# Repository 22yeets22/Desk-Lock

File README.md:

# Desk-Lock

A cheap desk lock that unlocks with an NFC card.

## Overview

This project is a DIY desk lock which keeps items in your desk secure by using a NFC reader. An ESP32 reads an NFC card via a PN532 module and controls a servo motor that locks or unlocks the desk. A photoresistor is used to detect when the drawer is closed so it can relock automatically.

[Detailed Description Here](#Detailed-Description)

## Motivation

I wanted a secure way to lock my desk because I keep important items inside and my little brother cannot be trusted with it. Buying a commercial lock felt boring and expensive, so building one with NFC was more interesting and let me design my own NFC card and reader.

## Parts List (Bill of Materials)

- 1x of [Photoresistor](https://www.aliexpress.us/item/3256805782399608.html), TYPE 5528, PRICE $2.39
- 1x of [10k Resistor](https://www.aliexpress.us/item/2251832766343175.html), TYPE 10K, PRICE $1.25
- 1x of [MG996R Servo](https://www.aliexpress.us/item/3256808293405785.html), TYPE N/A, PRICE $0.99
- 1x of [AC to DC Power Supply](https://www.aliexpress.us/item/3256806901002886.html), TYPE US Plug/DC 5V/4A, PRICE $4.60
- 1x of [ESP32 Development Board](https://www.aliexpress.us/item/3256805767190776.html), TYPE 1PCS-CP2102 TYPE-C, PRICE $6.56
- 1x of [PN532 NFC Module](https://www.aliexpress.us/item/3256806852006648.html), TYPE PN532, PRICE $3.67

### NFC Card - 25.33 for 5

| Schematic                                     | PCB                               | 3D View                         |
| --------------------------------------------- | --------------------------------- | ------------------------------- |
|  |  |  |

## Detailed Description

This project is a DIY NFC-based desk lock using an ESP32. A PN532 NFC reader communicates with the ESP32 over I2C to read NFC cards. When an authorized card is detected, the ESP32 drives a servo motor to unlock the drawer. Unauthorized cards are ignored.<br>
The servo is powered by an external supply that also powers the ESP32 and is mounted so one position locks the drawer and another unlocks it. The mechanical design is flexible and can support different desk types.<br>
A photoresistor inside the drawer is wired as a voltage divider with a 10 kΩ resistor and connected to an ESP32 ADC pin. It detects whether the drawer is open or closed based on light level. After unlocking, the system waits until the drawer is closed (becomes dark), then automatically relocks after a configurable delay (default 10 seconds).

## CAD

There is a case for every single part in this project:

- ESP32 Case: for the esp32 (duh)
- PHotoresistor Case: for the photoresistor + resistor setup to detect desk drawer close
- MG996R Case: Servo case for a wider base which improves adhesion + screw holes if you need it
- PN532 Case (Case + Lid): Case + lid for the nfc reader module
- And also, a full assembly with all electronics included!

## Example Placement Diagram

Here is an example placement diagram for the servo:

## Notes

The servo holder was not made by me, but suits the purpose perfectly.

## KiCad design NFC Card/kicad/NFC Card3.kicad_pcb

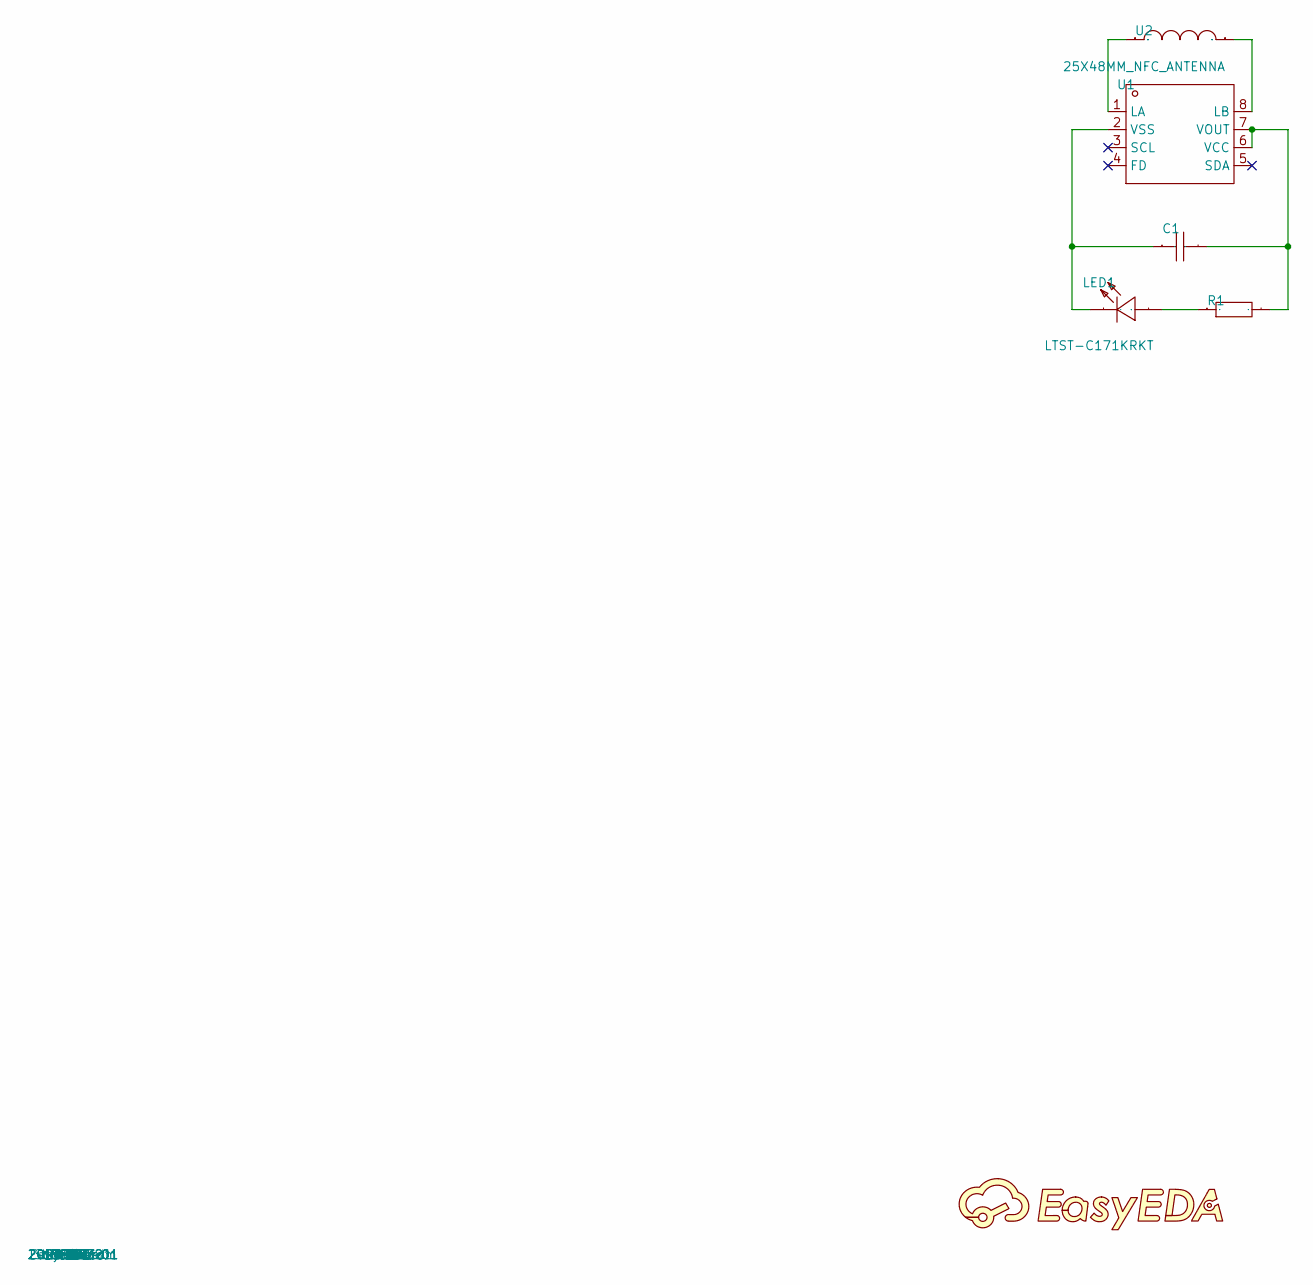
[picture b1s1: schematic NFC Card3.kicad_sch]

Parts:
C1: 220nF; C0603; Manufacturer Part CL10B224KA8NNNC; LCSC Part Name 220nF ±10% 25V
LED1: LTST-C171KRKT; LED-SMD_L2.0-W1.25-RD_RED; Manufacturer Part LTST-C171KRKT; LCSC Part Name 红灯
R1: 510Ω; R0402; Manufacturer Part RC0402FR-07510RL; LCSC Part Name 厚膜电阻 510Ω ±1% 62.5mW
U1: 13.56MHz; XQFN-8_L1.6-W1.6-P0.50-BL_NT3H2111W0FHKH; Manufacturer Part NT3H2111W0FHKH; LCSC Part Name NT3H2111W0FHKH
U2: 25X48MM_NFC_ANTENNA

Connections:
$1N430: U1.8 (LB), U2.P$2
$1N435: U1.1 (LA), U2.P$1
$1N518: C1.2, R1.2, U1.6 (VCC), U1.7 (VOUT)
$1N545: LED1.2 (A), R1.1
$1N550: C1.1, LED1.1 (C), U1.2 (VSS)

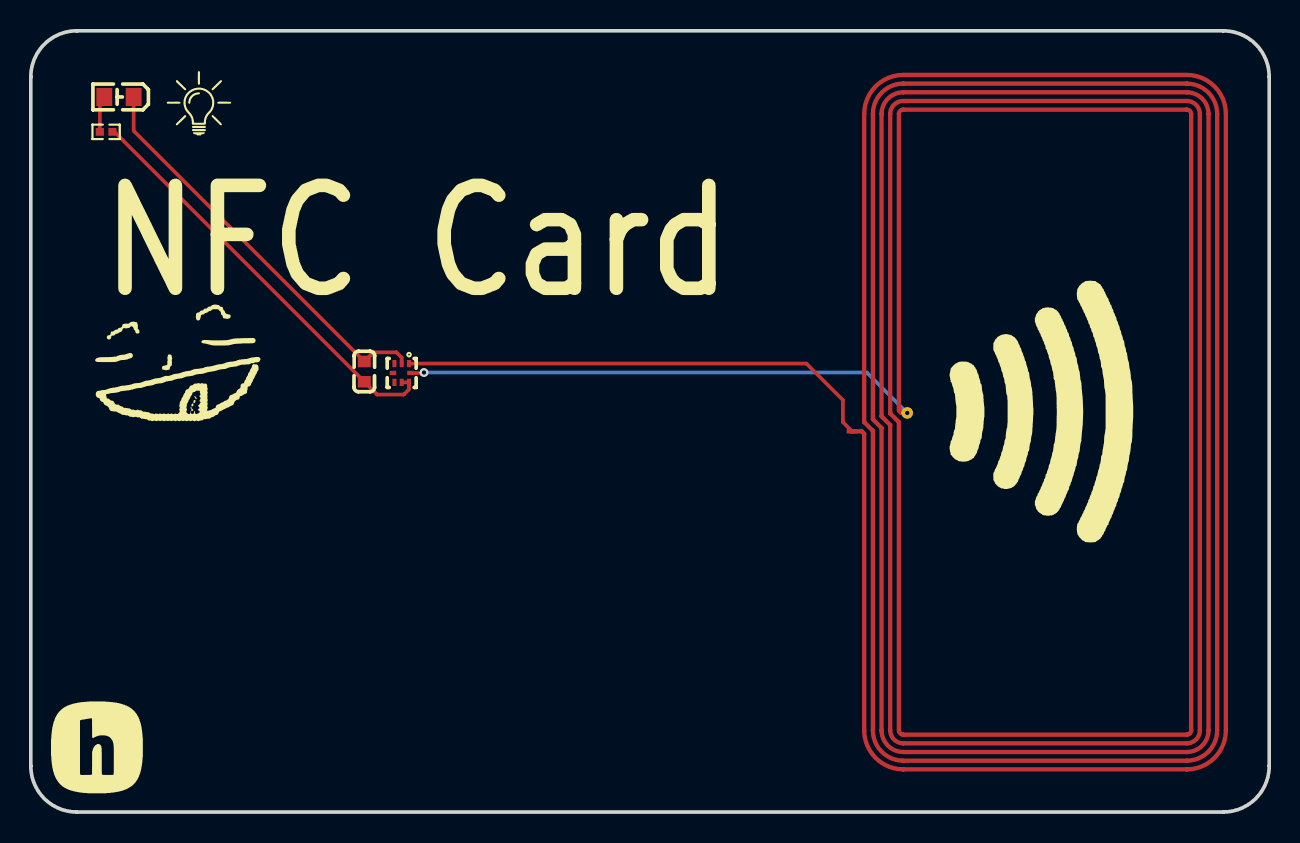
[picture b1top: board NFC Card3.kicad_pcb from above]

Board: 2 copper layers, 85.6 x 54.0 mm, 5 parts (0 on the bottom side), 5 nets.

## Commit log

2026-01-03 Initialize README with project info
    Add project title and description to README
2026-01-03 Add NFC drawer lock functionality
    Implement NFC-controlled drawer locking mechanism with light detection.
2026-01-03 Clarify comments for pin definitions and constants
    Updated comments for clarity on pin definitions and constants.
2026-01-03 Expand README with project details and motivation
    Added project overview and motivation for the desk lock.
2026-01-03 add bom + motivation to readme
2026-01-03 add .epro file
2026-01-03 readme
2026-01-04 Add BOM.csv with component details and pricing
2026-01-04 update .epro file,upload gerber and whatnot
2026-01-04 Add CUSTOM NFC CARD entry to BOM.csv
2026-01-04 Add price information for NFC Card
    Updated NFC Card section with price information.
2026-01-08 update ALL OF THE STINKIN NFC CARD FILES AND KICAD
2026-01-29 added cad files + images + readme detailed desc
2026-01-29 Add link to detailed description in README
2026-02-01 Update README with servo placement diagram
    Added an example placement diagram for the servo.
2026-02-01 new cad
2026-02-01 rename cad to be more specific
2026-02-23 restate that i indeed do, have cads for every single part
2026-02-23 1 sentence
